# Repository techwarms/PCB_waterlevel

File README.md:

These files contain PCB and schematic files for STM 32 for water level sensors.

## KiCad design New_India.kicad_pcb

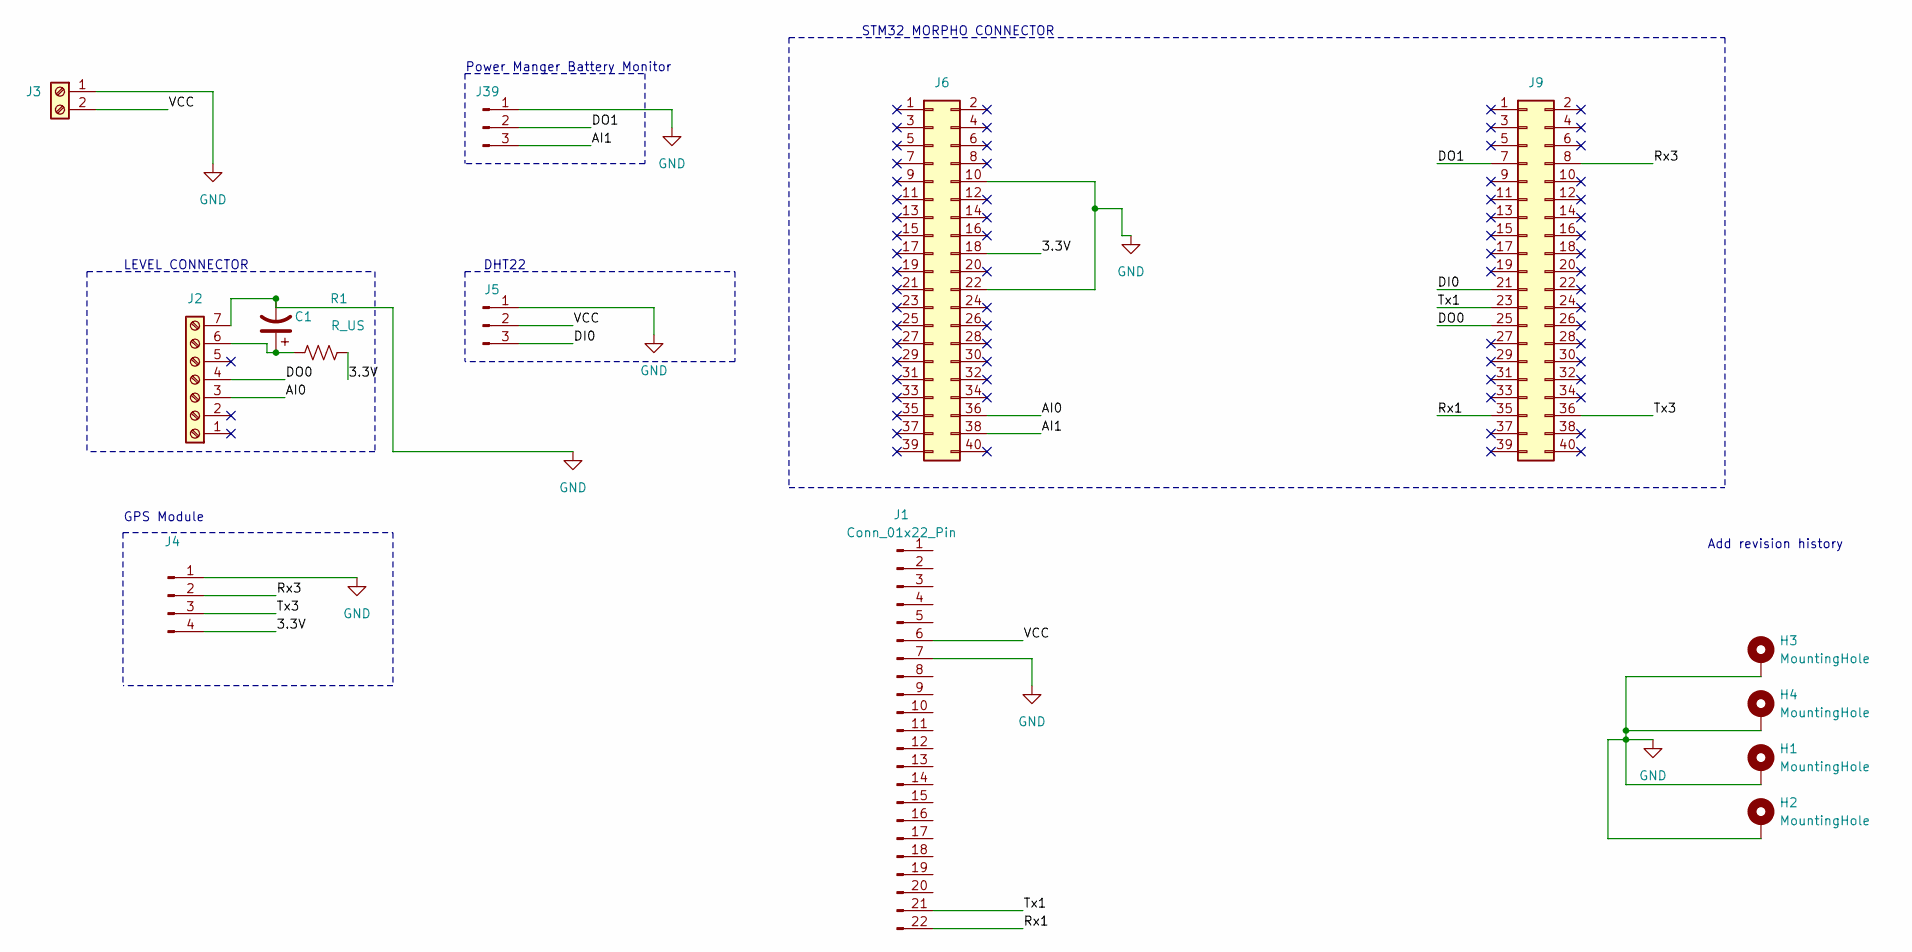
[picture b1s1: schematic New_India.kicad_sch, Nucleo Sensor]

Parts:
C1: C_Polarized_US; CP_Radial_D8.0mm_P3.50mm
H1, H2, H3, H4: MountingHole; MountingHole_2.5mm_Pad_TopBottom
J1: Conn_01x22_Pin; PinSocket_1x22_P2.54mm_Vertical
J2: Screw_Terminal_01x07; TerminalBlock_Phoenix_MPT-0,5-7-2.54_1x07_P2.54mm_Horizontal
J3: Screw_Terminal_01x02; TerminalBlock_Phoenix_MPT-0,5-2-2.54_1x02_P2.54mm_Horizontal
J4: Conn_01x04_Pin; PinSocket_1x04_P2.54mm_Vertical
J5: Conn_01x03_Pin; PinHeader_1x03_P2.54mm_Vertical
J6, J9: Connector_Generic_Conn_02x19_Odd_Even; PinSocket_2x20_P2.54mm_Vertical_custom
J39: Conn_01x03_Pin; JST_EH_S3B-EH_1x03_P2.50mm_Horizontal
R1: R_US; R_Axial_DIN0204_L3.6mm_D1.6mm_P5.08mm_Horizontal

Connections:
/3.3V: J4.4, J6.18, R1.2
/AI0: J2.3, J6.36
/AI1: J6.38, J39.3
/DI0: J5.3, J9.21
/DO0: J2.4, J9.25
/DO1: J9.7, J39.2
/Rx1: J1.22, J9.35
/Rx3: J4.2, J9.8
/Tx1: J1.21, J9.23
/Tx3: J4.3, J9.36
/VCC: J1.6, J3.2, J5.2
GND: C1.2, H1.1, H2.1, H3.1, H4.1, J1.7, J2.7, J3.1, J4.1, J5.1, J6.10, J6.22, J39.1
unnamed: C1.1, J2.6, R1.1

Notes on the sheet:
LEVEL CONNECTOR
GPS Module
Power Manger Battery Monitor
DHT22
Add revision history
STM32 MORPHO CONNECTOR

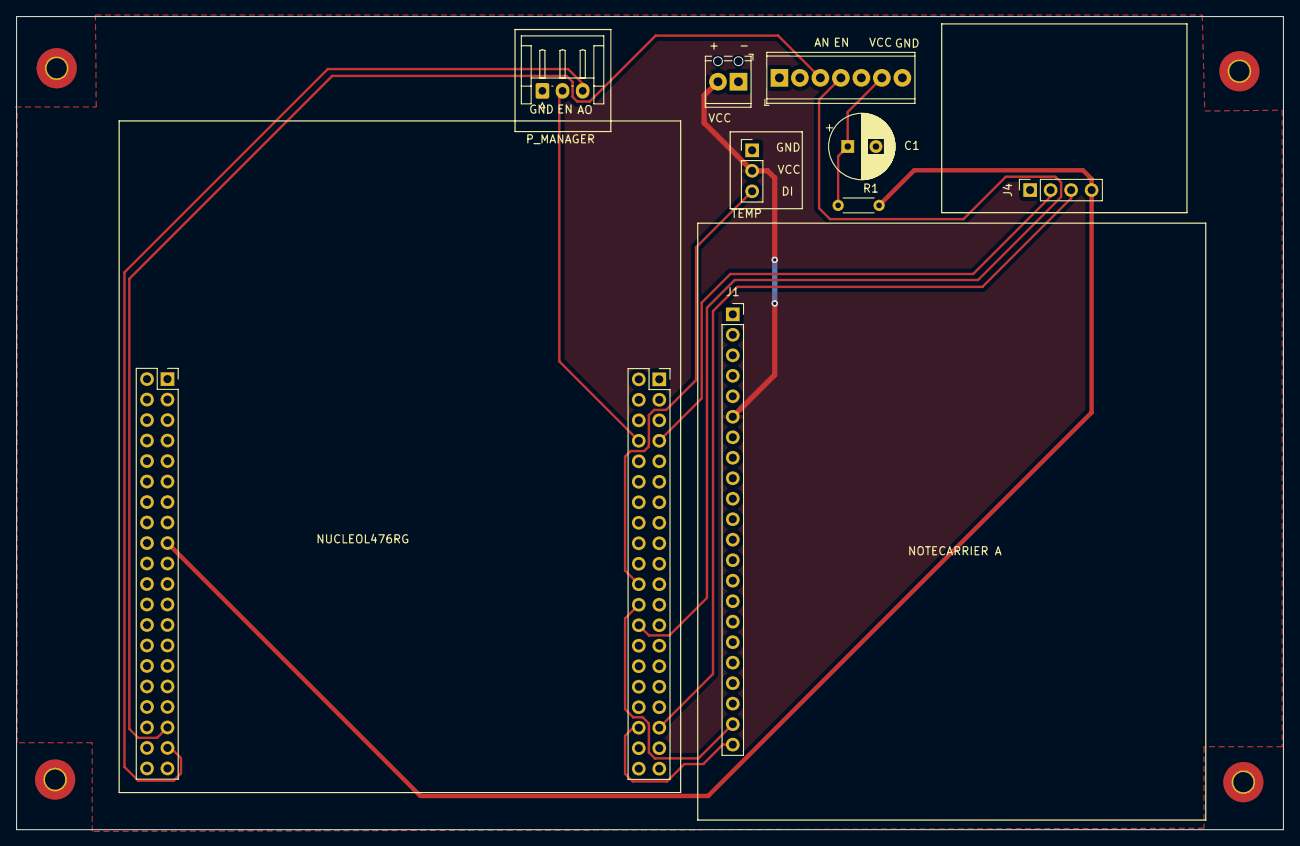
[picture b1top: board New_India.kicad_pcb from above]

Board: 2 copper layers, 157.0 x 100.8 mm, 14 parts (0 on the bottom side), 13 nets.
